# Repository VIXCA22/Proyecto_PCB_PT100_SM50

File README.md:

# Tarjeta de acondicionamiento de señales PT100 y SM-50

Diseño e implementación de una tarjeta de acondicionamiento de señales para sensores de torque y temperatura en un motor de inducción trifásico del LabCES. La PCB adapta las señales de un sensor de temperatura PT100 y un sensor de torque SM-50 para facilitar su adquisición y monitoreo dentro de un sistema de medición.

## Objetivo

Diseñar e implementar una tarjeta de circuito impreso que permita acondicionar y adaptar las señales provenientes de los sensores de torque y temperatura de un motor de inducción utilizado en el LabCES, con el propósito de facilitar su correcta adquisición y monitoreo para analizar el desempeño del motor.

## Objetivos específicos

1. Comprender los fundamentos básicos del diseño de tarjetas de circuito impreso y su aplicación al acondicionamiento de señales usando KiCad.
2. Verificar el funcionamiento de los sensores de torque y temperatura mediante simulaciones y pruebas experimentales.
3. Diseñar una PCB que integre el circuito necesario para acondicionar las señales de los sensores.
4. Implementar y probar el prototipo, evaluando su desempeño dentro del sistema de medición del motor de inducción en el LabCES.
5. Mantener un repositorio Git con archivos de diseño electrónico, documentación técnica e historial de desarrollo.

## Vista del diseño

### Esquemático KiCad

### PCB en KiCad

### PCB 3D

## Diagrama de bloques

Nota de adquisicion: la lectura maxima del ADC de la B-Box se toma como +/-5 V (10 V de span), por lo que la salida bipolar nominal del SM-50 se mantiene en +/-4.39 V para conservar margen de medicion.

## Simulaciones

### Canal PT100

### Canal SM-50

### Esquemáticos LTspice

[PDF PT100](docs/figuras/ltspice_pt100_esquematico.pdf)

[PDF SM-50](docs/figuras/ltspice_sm50_esquematico.pdf)

## Estructura del repositorio

| Ruta | Contenido |
| --- | --- |
| `PCB_PT100_SM50/` | Proyecto KiCad principal: esquemático, PCB, librerías locales, footprints y modelos 3D. |
| `ProyectoPCB_LTspice_PT100_SM50/` | Simulaciones LTspice de los canales PT100 y SM-50. |
| `docs/figuras/` | Imágenes/PDF del esquemático, PCB, vista 3D, LTspice y gráficas. |
| `docs/simulacion/` | CSV, resumen numérico y cálculos finales usados para las gráficas y tablas. |
| `docs/validacion/` | Reportes finales ERC/DRC. |
| `docs/fabricacion/` | ZIP Gerber final con archivo de taladros. |
| `docs/resumen/` | Resumen ejecutivo final del proyecto. |
| `docs/poster/` | Póster final usado para la presentación del proyecto. |
| `docs/bitacora/` | Bitácora actualizada del proceso, en PDF y fuente LaTeX. |
| `docs/referencias/` | Resumen de verificación de footprints y documentos de entrega conservados. |
| `scripts/` | Script para regenerar figuras de simulación y vistas documentales LTspice. |

## Estado final

- KiCad ERC: `0` errores, `0` advertencias.
- KiCad DRC: `0` violaciones, `0` pads desconectados, `0` errores de footprints.
- Paridad esquemático-PCB: `0` problemas.
- ZIP para fabricar: `docs/fabricacion/PCB_PT100_SM50_GERBERS_CON_DRILL.zip`.
- Reportes: `docs/validacion/erc_final_20260626.rpt` y `docs/validacion/drc_final_20260626.rpt`.

## Cómo revisar

1. Abrir `PCB_PT100_SM50/PCB_PT100_SM50.kicad_pro` en KiCad 9.
2. Ejecutar ERC desde el editor esquemático.
3. Ejecutar DRC con comprobación de paridad esquemático-PCB desde el editor PCB.
4. Revisar las simulaciones en `ProyectoPCB_LTspice_PT100_SM50/`.
5. Subir a fabricación el ZIP `docs/fabricacion/PCB_PT100_SM50_GERBERS_CON_DRILL.zip` si se requiere fabricar esta revisión.

## Documentación

- [Reporte formal IEEE PCB PT100/SM-50](docs/reporte_ieee/ReporteFormalPCB_PT100_SM50.pdf)
- [Informe de desarrollo del proyecto](docs/INFORME_DESARROLLO_PROYECTO.md)
- [Resumen ejecutivo](docs/resumen/ResumenEjecutivoKDVJC09331.pdf)
- [Proceso de diseño y trazabilidad](docs/PROCESO_DISENO_TRAZABILIDAD.md)
- [Bitácora actualizada del proyecto](docs/bitacora/bitacora_PCB_actualizada_27_06_2026.pdf)
- [Póster final](docs/poster/vizcaino-jimenez.pdf)
- [Validación final](docs/VALIDACION.md)
- [Referencias técnicas y footprints](docs/REFERENCIAS_TECNICAS.md)

## Herramientas

- KiCad 9.0.7
- LTspice
- Python 3 para generar figuras documentales
- Git / GitHub

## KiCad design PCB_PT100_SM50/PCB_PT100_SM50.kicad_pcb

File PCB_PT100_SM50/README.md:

# Proyecto KiCad - PCB PT100 y SM-50

Esta carpeta contiene el diseno KiCad principal de la tarjeta de acondicionamiento de senales para sensores PT100 y SM-50.

## Archivos principales

| Archivo o carpeta | Uso |
| --- | --- |
| `PCB_PT100_SM50.kicad_pro` | Proyecto KiCad principal. |
| `PCB_PT100_SM50.kicad_sch` | Esquematico del circuito de acondicionamiento. |
| `PCB_PT100_SM50.kicad_pcb` | Layout de la PCB. |
| `symbols/` | Librerias de simbolos locales. |
| `footprints/` | Huellas locales usadas por la PCB. |
| `3d/` | Modelos 3D vinculados a las huellas. |
| `bom/` | Lista de materiales y referencia de compra. |
| `docs/` | Imagenes y soporte visual del diseno. |
| `outputs/` | Reportes de validacion generados por KiCad. |

## Estado de validacion

El cierre de validacion documentado fue generado con KiCad 9 y no reporta violaciones:

```text
../docs/validacion/erc_final_20260626.rpt
../docs/validacion/drc_final_20260626.rpt
```

La carpeta `outputs/` conserva reportes locales intermedios del PCB. Los reportes anteriores con warnings eran de sincronizacion de librerias, no de conexion electrica. Se registro la libreria faltante `ProyectoPCB` y se dejo la regla `lib_symbol_mismatch` en `ignore` porque varios simbolos fueron ajustados localmente para el esquematico.

## Uso rapido

1. Abrir `PCB_PT100_SM50.kicad_pro` en KiCad 9.
2. Revisar el esquematico y correr ERC.
3. Revisar el PCB y correr DRC antes de fabricar.
4. Usar las librerias locales incluidas en `sym-lib-table` y `fp-lib-table`.

## Nota sobre LTspice

Los archivos `.asy` y `.lib` pertenecen a simulacion LTspice. No se deben importar como simbolos o footprints KiCad; para KiCad se usan `.kicad_sym`, `.kicad_mod` y modelos `.step/.wrl`.

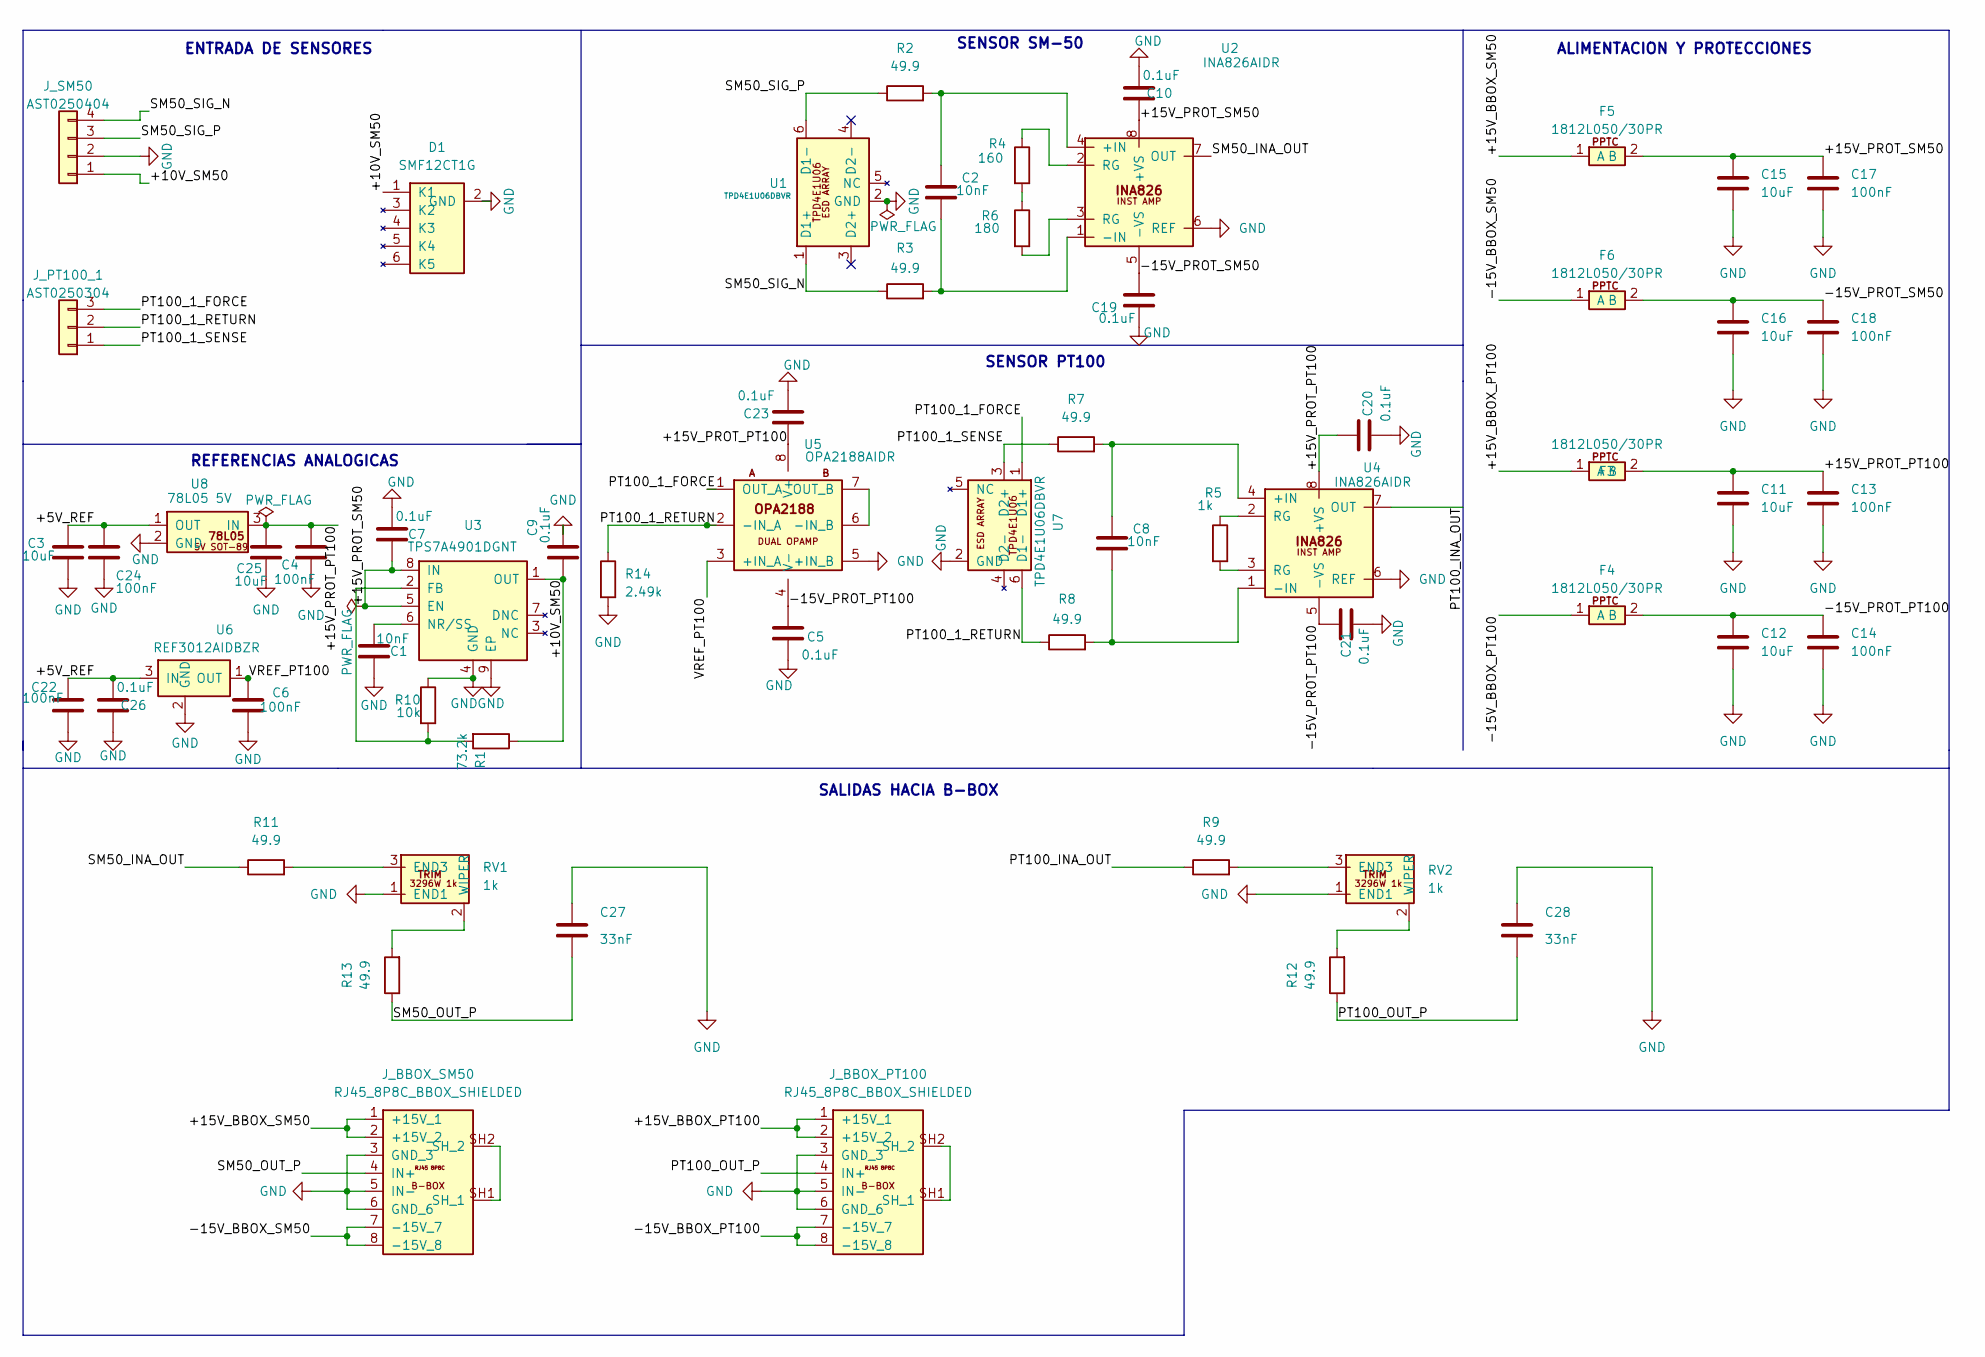
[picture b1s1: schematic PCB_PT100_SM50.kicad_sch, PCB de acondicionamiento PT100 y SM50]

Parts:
C1, C2, C8: 10nF; C_0805_2012Metric
C3, C11, C12, C15, C16, C25: 10uF; C_0805_2012Metric
C4, C6, C13, C14, C17, C18, C22, C24: 100nF; C_0805_2012Metric
C5, C7, C9, C10, C19, C20, C21, C23, C26: 0.1uF; C_0805_2012Metric
C27, C28: 33nF; C_0805_2012Metric
D1: SMF12CT1G; SMF12CT1G_SC88_SOT363
F3, F4, F5, F6: 1812L050/30PR; PPTC_1812L050_30PR_1812
J_BBOX_PT100: RJ45_8P8C_BBOX_SHIELDED; BEL_2250066-1
J_BBOX_SM50: RJ45_8P8C_BBOX_SHIELDED; BEL_2250066-1
J_PT100_1: AST0250304; CONN_AST0250304_MZC
J_SM50: AST0250404
R1: 73.2k; R_0805_2012Metric
R2, R3, R7, R8, R9, R11, R12, R13: 49.9; R_0805_2012Metric
R4: 160; R_0805_2012Metric
R5: 1k; R_0805_2012Metric
R6: 180; R_0805_2012Metric
R10: 10k; R_0805_2012Metric
R14: 2.49k; R_0805_2012Metric
RV1, RV2: 1k; Potentiometer_Bourns_3296W_Vertical
U1, U7: TPD4E1U06DBVR; SOT-23-6
U2, U4: INA826AIDR; SOIC-8_3.9x4.9mm_P1.27mm
U3: TPS7A4901DGNT; TPS7A4901DGNT_DGN8_1P89X1P57
U5: OPA2188AIDR; SOIC-8_3.9x4.9mm_P1.27mm
U6: REF3012AIDBZR; SOT-23
U8: 78L05 5V; SOT-89-3

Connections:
/+5V_REF: C3.1, C22.1, C24.1, C26.2, U6.3 (IN), U8.1 (OUT)
/+10V_SM50: C9.1, D1.1 (K1), J_SM50.1, R1.1, U3.1 (OUT)
/+15V_BBOX_PT100: F3.1 (A), J_BBOX_PT100.1 (+15V_1), J_BBOX_PT100.2 (+15V_2)
/+15V_BBOX_SM50: F5.1 (A), J_BBOX_SM50.1 (+15V_1), J_BBOX_SM50.2 (+15V_2)
/+15V_PROT_PT100: C4.1, C11.1, C13.1, C20.1, C23.1, C25.1, F3.2 (B), U4.8 (+VS), U5.8 (V+), U8.3 (IN)
/+15V_PROT_SM50: C7.1, C10.1, C15.1, C17.1, F5.2 (B), U2.8 (+VS), U3.5 (EN), U3.8 (IN)
/-15V_BBOX_PT100: F4.1 (A), J_BBOX_PT100.7 (-15V_7), J_BBOX_PT100.8 (-15V_8)
/-15V_BBOX_SM50: F6.1 (A), J_BBOX_SM50.7 (-15V_7), J_BBOX_SM50.8 (-15V_8)
/-15V_PROT_PT100: C5.1, C12.1, C14.1, C21.1, F4.2 (B), U4.5 (-VS), U5.4 (V-)
/-15V_PROT_SM50: C16.1, C18.1, C19.1, F6.2 (B), U2.5 (-VS)
/PT100_1_FORCE: J_PT100_1.3, U5.1 (OUT_A), U7.1 (D1+)
/PT100_1_RETURN: J_PT100_1.2, R8.1, R14.1, U5.2 (-IN_A), U7.6 (D1-)
/PT100_1_SENSE: J_PT100_1.1, R7.1, U7.3 (D2+)
/PT100_INA_OUT: R9.1, U4.7 (OUT)
/PT100_OUT_P: C28.2, J_BBOX_PT100.4 (IN+), R12.1
/SM50_INA_OUT: R11.1, U2.7 (OUT)
/SM50_OUT_P: C27.2, J_BBOX_SM50.4 (IN+), R13.1
/SM50_SIG_N: J_SM50.4, R3.1, U1.1 (D1+)
/SM50_SIG_P: J_SM50.3, R2.1, U1.6 (D1-)
/VREF_PT100: C6.1, U5.3 (+IN_A), U6.1 (OUT)
GND: C1.1, C3.2, C4.2, C5.2, C6.2, C7.2, C9.2, C10.2, C11.2, C12.2, C13.2, C14.2, C15.2, C16.2, C17.2, C18.2, C19.2, C20.2, C21.2, C22.2, C23.2, C24.2, C25.2, C26.1, C27.1, C28.1, D1.2 (GND), J_BBOX_PT100.3 (GND_3), J_BBOX_PT100.5 (IN-), J_BBOX_PT100.6 (GND_6), J_BBOX_SM50.3 (GND_3), J_BBOX_SM50.5 (IN-), J_BBOX_SM50.6 (GND_6), J_SM50.2, R10.1, R14.2, RV1.1 (END1), RV2.1 (END1), U1.2 (GND), U2.6 (REF), U3.4 (GND), U3.9 (EP), U4.6 (REF), U5.5 (+IN_B), U6.2 (GND), U7.2 (GND), U8.2 (GND); also elsewhere on the board
unnamed: J_BBOX_PT100.SH1 (SH_1), J_BBOX_PT100.SH2 (SH_2)
unnamed: J_BBOX_SM50.SH1 (SH_1), J_BBOX_SM50.SH2 (SH_2)
unnamed: R4.1, U2.2 (RG)
unnamed: R4.2, R6.1
unnamed: R5.1, U4.2 (RG)
unnamed: R5.2, U4.3 (RG)
unnamed: R6.2, U2.3 (RG)
unnamed: R11.2, RV1.3 (END3)
unnamed: R13.2, RV1.2 (WIPER)
unnamed: R9.2, RV2.3 (END3)
unnamed: R12.2, RV2.2 (WIPER)
unnamed: C2.1, R2.2, U2.4 (+IN)
unnamed: C2.2, R3.2, U2.1 (-IN)
unnamed: R1.2, R10.2, U3.2 (FB)
unnamed: C1.2, U3.6 (NR/SS)
unnamed: C8.1, R7.2, U4.4 (+IN)
unnamed: C8.2, R8.2, U4.1 (-IN)
unnamed: U5.6 (-IN_B), U5.7 (OUT_B)

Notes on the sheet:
SENSOR PT100
SALIDAS HACIA B-BOX
SENSOR SM-50
ALIMENTACION Y PROTECCIONES
ENTRADA DE SENSORES
REFERENCIAS ANALOGICAS

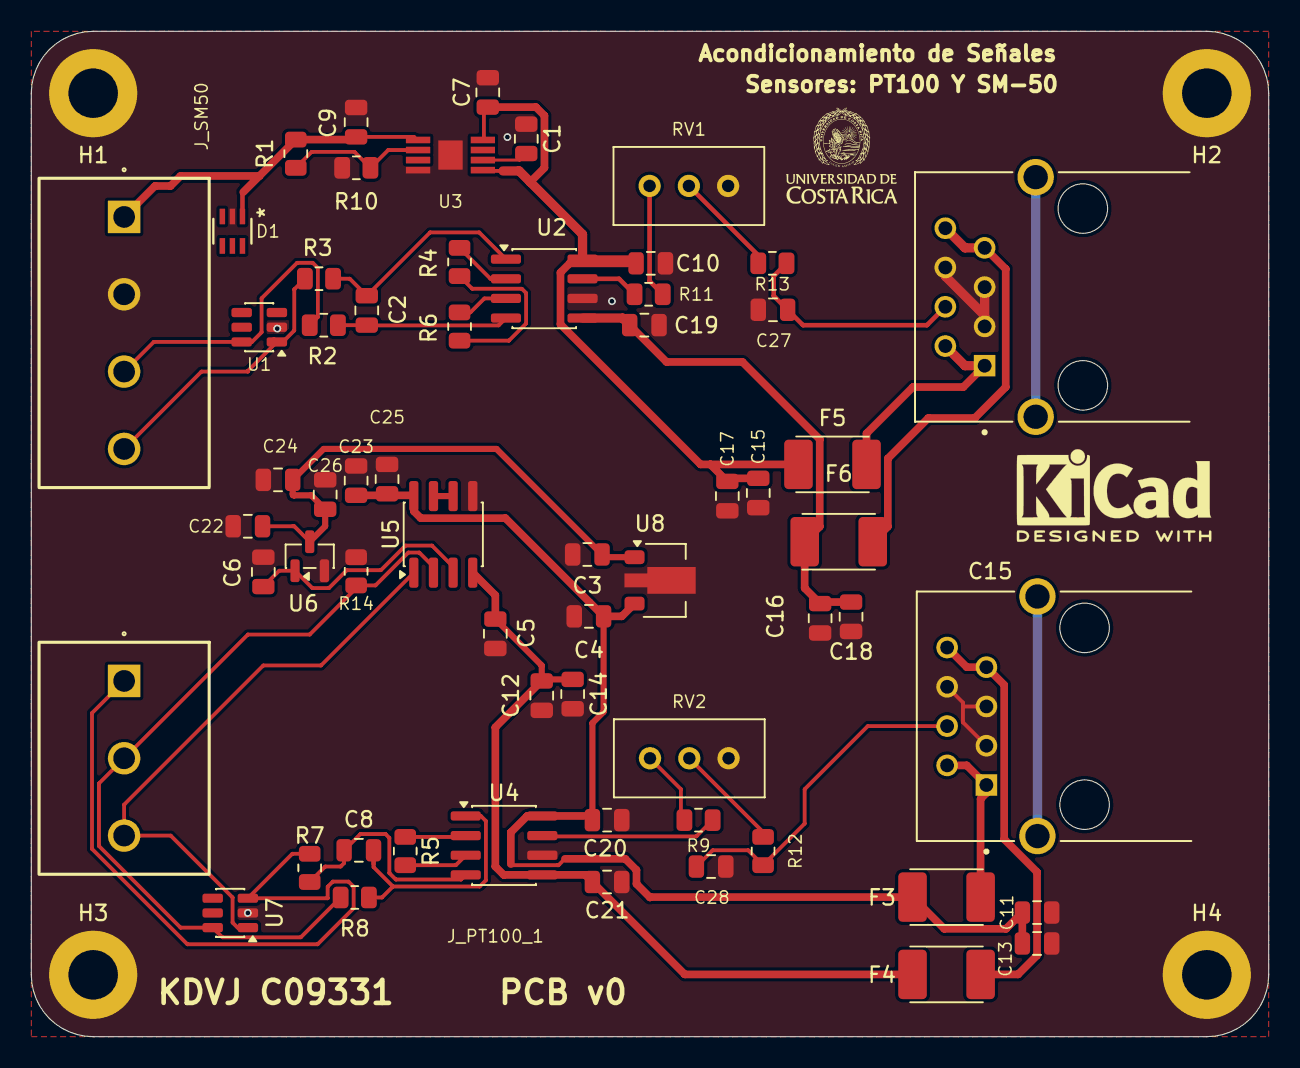
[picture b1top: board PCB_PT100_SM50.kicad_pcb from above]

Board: 2 copper layers, 80.0 x 65.0 mm, 65 parts (0 on the bottom side), 39 nets.

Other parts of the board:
H1, H2, H3, H4: MountingHole_3.2mm_M3_ISO7380_Pad

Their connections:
GND: H1.1, H2.2, H3.3, H4.4; also elsewhere on the board

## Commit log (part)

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2026-06-24 Prepare PCB project for GitHub delivery
2026-06-26 Publish final PCB project
2026-06-26 Correct simulation figures
2026-06-26 Update PCB 3D front view
2026-06-27 Update LTspice schematics and fabrication outputs
2026-06-27 Fix PCB 3D view orientation
2026-06-27 Fix PCB editor image crop
2026-06-27 Arreglando errores de ortografíia en le README
    Corrige errores de acentuación y ortografía en el README.
2026-06-27 Fix spelling and accentuation in README.md
    Corrected spelling and accentuation errors in the README content, ensuring proper terminology and clarity.
2026-06-27 Fix typo in README.md description
2026-06-27 Fix PCB 3D image orientation
2026-06-27 Center PCB 2D image in README
2026-06-27 Add project development report
2026-06-27 Expand report with full reference package
2026-06-27 Clean AI references and polish Spanish docs
2026-06-27 Add final sensor calculations and references
2026-06-27 Set PCB 3D image to frontal view
2026-06-27 Use provided PCB 3D top render
2026-06-27 Add updated project logbook
2026-06-27 Add final project poster
2026-06-29 Restaurar version SM-50 0-5V
2026-06-29 Actualizar figuras SM-50 0-5V
2026-06-29 Reemplazar render 3D del PCB
2026-06-29 Documentar limite ADC B-Box +/-5V
2026-06-29 Actualizar documentos finales
2026-06-30 Actualizar salida bipolar SM-50
